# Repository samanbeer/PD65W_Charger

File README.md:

# PD65W Smart Charger 

---

## Project Overview

- **What is it?**  It is a fast 65W charger with Powerdelivery, but its SMART! It has XIAO RP2040 MCU inside and if you want to know more then read more below! 
- **What does it do?**  Belive or not its charging phone :O   Well, it is also charging modern notebooks and all other things, that have USB-C, with a maximum power of 65W which is really good. And WHILE it is charging your device, the RP2040 is with help of INA226 chip measuring input/output Voltage and Current and displaing it on 128x32 display. 
Also the chragers can be really hot while charging, but not this one. Why? Because this one has a FAN! And if the RP2040 starts to measure big temperature on thermistors then it will adjust FAN speed to cool it off.
- **Why does it exist?** Because normal charger from shops are boring, and with this charger you can see how much current and how big voltage is flowing to your phone! But also a good point why does this exist is to **reuse** old adapters from laptops or routers that have 9-24V.

---

## Why I Made This

A few months ago, I bought a small PD65W module on AliExpress to charge my phone and laptop from old 20V laptop adapter. I designed a simple 3D printed enclosure for it (which I also shared on [MakerWorld](https://makerworld.com/en/models/3175390-mini-pd-65w-trigger-charger-8-30v-case#profileId-3590634)). 

But when I connected a 65W power bank, and it was running at max power, the module and adapter was extremely hot! I also taped 10kΩ thermistor on the top of the power source on surface and I measured with multimeter temperatures over 55°C, and the internal heat was melting the PLA enclosure. And yes, I could just print it in PETG or ASA but that would not solve problem for this extreme heat.

That inspired me to build a complete, custom PCB based smart charger that fixes issues of that old setup:

1. **Cooling:** Added a 25x25x6mm 5V fan with holes for intake and exhaust
2. **2 Thermistors:** One thermistor is directly on the PD65W module, and second one is monitoring enclosure temperature
3. **OLED Display:** "0.91" OLED screen displays input voltage, input current, output voltage, output current, total wattage, temperatures, and fan speed **All in real time**.
5. **And lot more**

---

## Project Gallery

### 3D PCB Renders

### 3D Board Views

### PCB Layout & Schematic

### 3D Enclosure (Fusion 360)
*Custom 3D printable enclosure designed in Fusion 360. All CAD and 3D model files (`.f3z`, `.step`) are located in the [`CAD/`](CAD/) folder.*

---

### Schematic Blocks:

1. **AP63205 Step-Down Regulator:**
   - Steps down the 9V–24V DC input to a stable, clean **5.0V** (up to 2A) to power the XIAO RP2040, the 0.91" OLED display, and the 5V fan.
   - Uses a 4.7µH high-current power inductor (`L1`) and ceramic filter capacitors (`C2`, `C3`, `C4`).
2. **INA226:**
   - Sits on the primary input DC track through a precision 10mΩ (2512 size) shunt resistor (`R5`).
   - Communicates with the RP2040 over I2C (Address `0x40`), providing millivolt and milliamp precision for input power measurements.
3. **Output Voltage and Power calculation:**
   - A 100kΩ / 10kΩ precision resistor divider (`R6`, `R7`) scales down the 0V–20V USB-PD output rail to a safe 0V–1.82V signal for the RP2040 ADC (`A2`).
   - The firmware combines measured input power with known module conversion efficiency (~92%) and measured output voltage to calculate real time output current and power.
4. **2 Thermistors and Intelligent Fan:**
   - The cooling fan is controlled through a 2N2222 transistor (`Q1`) with a 1N4148 flyback diode (`D1`). If temperatures stay under 35°C, the fan stays completely silent (0% PWM). Between 35°C and 60°C, the fan dynamically scales speed (70–255 PWM). If temperature exceeds 60°C, the fan spins up at full 100% speed.

---

## Assembly Guide

### Required Tools & Materials
- Soldering iron 
- Some good solder wire
- Solder flux 
- Tweezers
- 3D Printer (for printing the Fusion 360 case in PETG, ABS, or PLA)
- Thermal paste or thermal conductive tape (for NTC thermistor contact)

### Assembly Steps

1. **Solder SMD ICs (U4, U5):**
   - Apply flux to the footprint pads of the **AP63205** (U4, TSOT-23-6) and **INA226** (U5, TSSOP-10).
   - Tack one corner pin, align all pins accurately under magnification, and solder the remaining pins.
2. **Solder SMD Passives & Inductor:**
   - Solder the 10mΩ 2512 shunt resistor (`R5`).
   - Solder 0805 SMD resistors (`R1–R4`, `R6–R9`) and capacitors (`C1–C6`).
   - Solder the 4.7µH power inductor (`L1`).
3. **Solder Through-Hole Components:**
   - Solder the 2N2222 transistor (`Q1`), 1N4148 diode (`D1`), and 2-pin Fan pin header (`J3`).
   - Solder the DC Barrel Jack (`J1`). There must be a good contact so put a lot of solder here.
4. **Modules:**
   - Solder the **XIAO RP2040** (`U3`) using female headers or solder direct-to-board as a SMD.
   - Solder the **PD65W Module** (`U1`) and connect the power output feedback wire (`J2`) between the module's positive output terminal and the voltage divider pad.
   - Mount the **0.91" I2C OLED Display** (`U2`) to the I2C header pins.
5. **Thermistors (TH1, TH2):**
   - Solder the thermistor.
   - Fasten `TH1` against the PD65W module power inductor/MOSFETs using thermal tape.
   - Position `TH2` near the board center to monitor ambient enclosure temperature.
6. **Final Case & Fan Assembly:**
   - Mount the 25mm 5V fan into the 3D-printed enclosure exhaust port and plug its 2-pin connector into `J3`.
   - Place the PCB and OLED into the case mounting hole and fasten with some tape.

---

## Firmware & Software Setup

### 1. Required Libraries
Install the following libraries via the Arduino IDE Library Manager:
- `INA226_WE` (by Wolfgang Ewald)
- `Adafruit GFX Library` (by Adafruit)
- `Adafruit SSD1306` (by Adafruit)
- `Wire` (Standard I2C library) - should be included

### 2. Flashing the XIAO RP2040
1. Connect the Seeed XIAO RP2040 to your computer via USB-C while holding down the **`BOOT`** button (or select the board port in Arduino IDE).
2. Select Board: **Seeed Studio XIAO RP2040** 
3. Open [`Firmware/code.ino`](Firmware/code.ino).
4. Click **Upload**.
5. Once uploaded, the OLED will start and will show all tha data.

### 3. OLED Telemetry Display Breakdown

```text
+-----------------------+
| IN :  24.00V  3.20A   |  <-- DC Barrel Jack Input
| OUT:  20.00V  2.95A   |  <-- USB-PD Output to Device
| PWR:  62.4W           |  <-- Total Active Power
| T1:42C T2:36C FAN:45% |  <-- Module Temp, Board Temp, Fan speed
+-----------------------+
```

---

## 📦 Bill of Materials (BOM)

> Sourced from [TME.eu](https://tme.eu), [AliExpress](https://aliexpress.com)

| Reference | Qty | Value / Component | Footprint / Package | Source / Link | Cost (USD) |
| :--- | :---: | :--- | :--- | :--- | :---: |
| **C1, C4, C5** | 3 | 100nF 50V MLCC | 0805 SMD | [TME Link](https://www.tme.eu/cz/details/cc0805krx7r9bb104/kondenzatory-mlcc-smd/yageo/) | $0.65 |
| **C2, C6** | 2 | 10µF 50V MLCC | 0805 SMD | [TME Link](https://www.tme.eu/cz/details/c2012x5r1v106kac/kondenzatory-mlcc-smd/tdk/c2012x5r1v106k125ac/) | $1.10 |
| **C3** | 1 | 22µF 16V MLCC | 0805 SMD | [TME Link](https://www.tme.eu/cz/details/cl21a226kpclrnc/kondenzatory-mlcc-smd/samsung/) | $0.39 |
| **D1** | 1 | 1N4148 Fast Switching Diode | DO-35 / DO-41 THT | [TME Link](https://www.tme.eu/cz/details/1n4148-cdi/univerzalni-diody-tht/cdil/1n4148/) | $0.1 |
| **J1** | 1 | DC Barrel Jack | Horizontal THT Barrel Jack | [TME Link](https://www.tme.eu/cz/details/fcr681465p/konektory-dc/cliff/fc681465p-dc-10lp/) | $2.42 |
| **J3** | 1 | 2-Pin Fan Header (2.54mm) + Sunon 5V Fan | PinHeader 1x02 + 25x25x6mm Fan | [TME Link](https://www.tme.eu/cz/details/mf25060v1-a99-a/ventilatory-dc-5v/sunon/mf25060v1-1000u-a99/) | $7.90 |
| **L1** | 1 | 4.7µH Power Inductor | SMD 6.3x6.3mm (LSXND6060) | [TME Link](https://www.tme.eu/cz/details/lsxnd6060yel4r7nmg/tlumivky/taiyo-yuden/) | $0.50 |
| **Q1** | 1 | 2N2222 NPN Transistor | TO-92 THT | [TME LInk](https://www.tme.eu/cz/details/2n2222a-dio/tranzistory-npn-tht/diotec-semiconductor/2n2222a/) | $0.90 |
| **R1, R2, R3, R4, R7, R9** | 6 | 10kΩ | 0805 SMD | [TME Link](https://www.tme.eu/cz/details/crcw080510k0fkea/rezistory-smd/vishay/) | $0.084 |
| **R5** | 1 | 10mΩ (0.010Ω) 1% Current Shunt | 2512 High-Power SMD | [TME Link](https://www.tme.eu/cz/details/mar251202fr010s/rezistory-smd/wayon/) | $1.98 |
| **R6** | 1 | 100kΩ 1% Resistor | 0805 SMD | [TME Link](https://www.tme.eu/cz/details/rc0805fr-07100k/rezistory-smd/yageo/rc0805fr-07100kl/) | $0.070 |
| **R8** | 1 | 1kΩ 1% Resistor | 0805 SMD | [TME Link](https://www.tme.eu/cz/details/rc0805fr-071k/rezistory-smd/yageo/rc0805fr-071kl/)  | $0.042 |
| **TH1, TH2** | 2 | 10kΩ NTC Thermistors (B=3950) | Radial / Axial THT | [TME Link](https://www.tme.eu/cz/details/b57891m0103j000/merici-termistory-ntc-tht/tdk/) | $1.45 |
| **U1** | 1 | PD65W USB-C PD Step-Down Module | Custom Module Footprint | [AliExpress Link](https://www.aliexpress.com/item/1005012593373561.html) | $6.00 |
| **U2** | 1 | 0.91" I2C Monochrome OLED Display | 4-Pin I2C Module Header | [AliExpress Link](https://www.aliexpress.com/item/1005008918700196.html) | $5.50 |
| **U3** | 1 | Seeed Studio XIAO RP2040 MCU | XIAO DIP-14 Module | [TME Link](https://www.tme.eu/cz/details/seeed-102010428/vyvojove-kity-ostatni/seeed-studio/xiao-rp2040/) | $7.00 |
| **U4** | 1 | AP63205WU 5V 2A Buck Regulator | TSOT-23-6 SMD | [AliExpress Link](https://www.aliexpress.com/item/1005006407229203.html) | $4.00 |
| **U5** | 1 | INA226AIDGSR Power Monitor IC | TSSOP-10 SMD | [TME Link](https://www.tme.eu/cz/details/ina226aidgsr/operacni-zesilovace-smd/texas-instruments/) | $6.00 |
| **PCB** | 1 | 2-Layer Custom FR-4 PCB (1.6mm) | Custom KiCad Design | [JLCPCB](https://jlcpcb.com) | $9.53 |
| **Shipping** | - | Combined Estimated Shipping | - | AliExpress & TME.eu | ~$10.00 |
| **Total** | | | | | **~$65.62** |

>btw you can import every components that is from TME directly to TME cart with this file: [quick_order_TME.csv](PCB/quick_order_TME.csv) 

---

## 🚀 How to Use

1. **Connect DC Power:** Plug any 9V to 24V DC power source (almost every old laptop charger) into the rear barrel jack `J1`.
2. **System Initialization:** The OLED display will lights up, showing the measured input voltages and temperatures.
3. **Charge your Device!:** Just connect anything you have with USB-C! (even laptops)
4. **Automatic Cooling:** Under heavy sustained loads (e.g., 45W–65W), the internal fan will automatically spin up smoothly based on thermistor readings, keeping components well within safe operating temperatures.

---

- Designed by **Šámot** in [Hack Club Forge](https://forge.hackclub.com/projects/1660) project.

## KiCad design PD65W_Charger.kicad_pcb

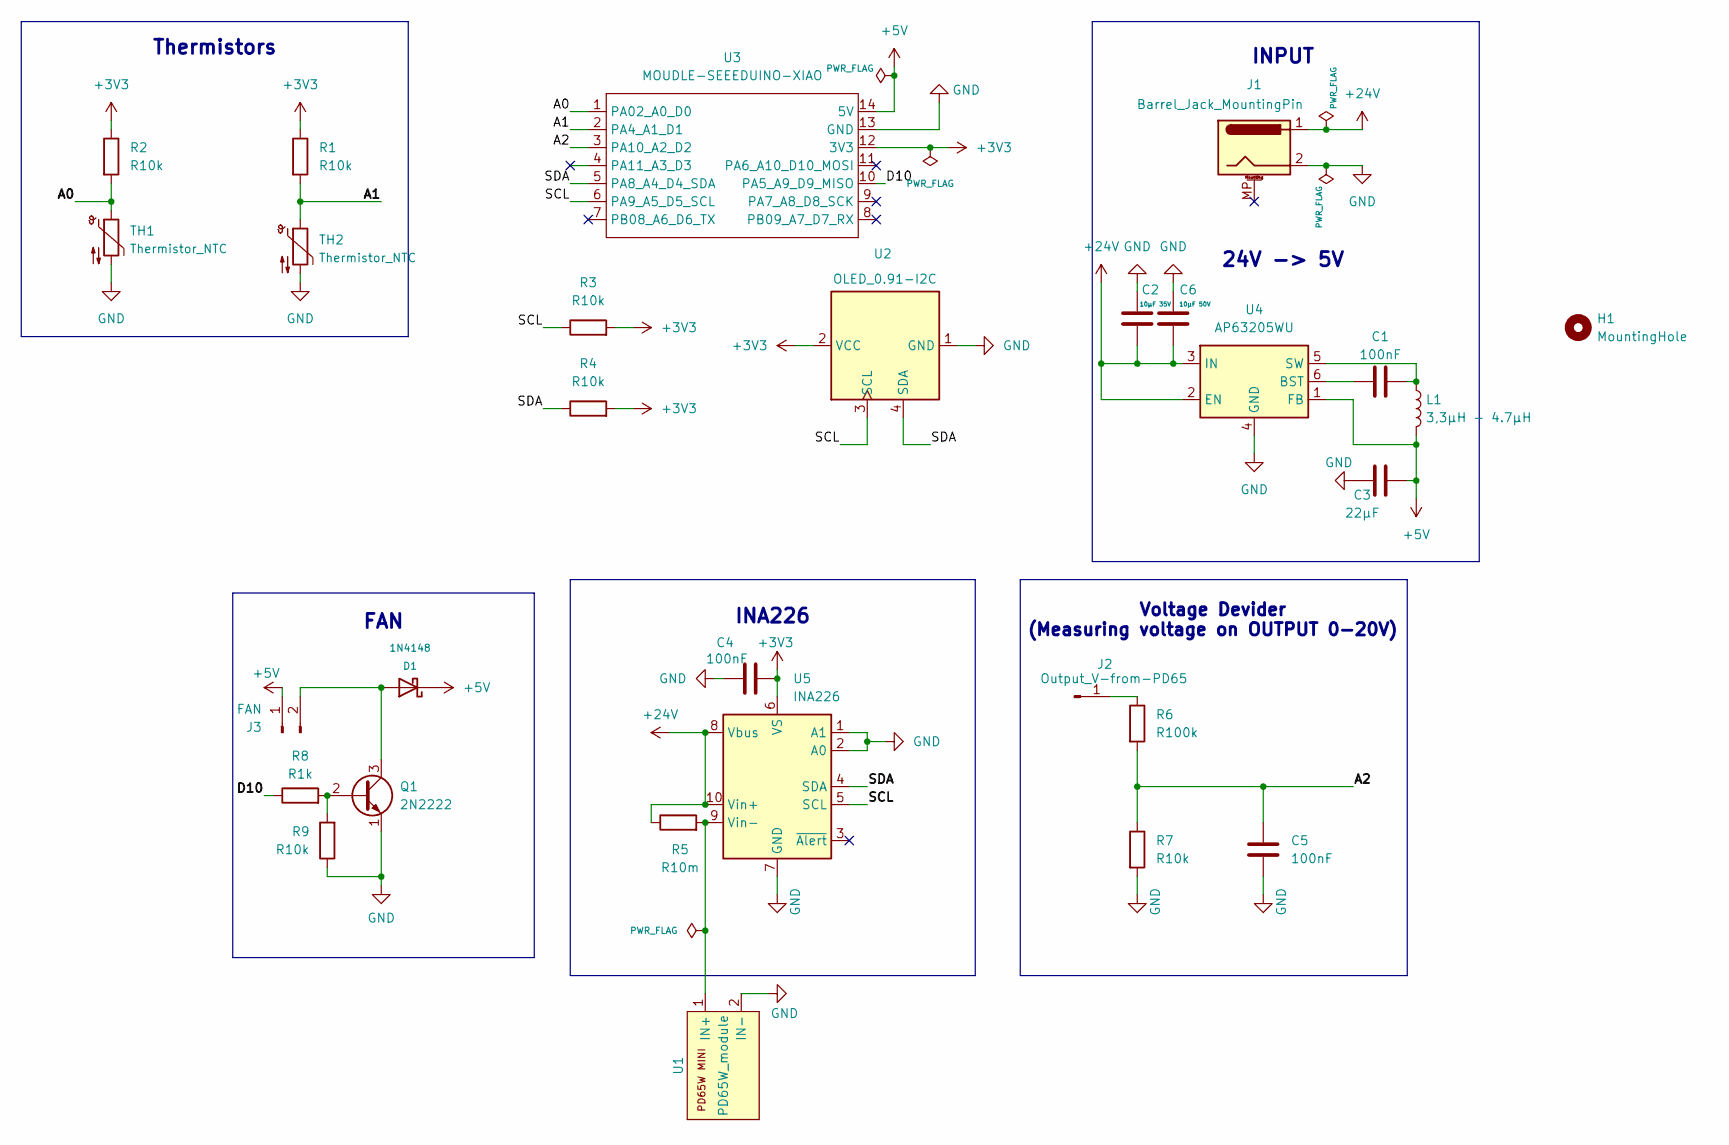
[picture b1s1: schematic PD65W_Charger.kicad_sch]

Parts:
C1, C4, C5: 100nF; C_0805_2012Metric_Pad1.18x1.45mm_HandSolder
C2: 10µF 35V; C_0805_2012Metric_Pad1.18x1.45mm_HandSolder
C3: 22µF; C_0805_2012Metric_Pad1.18x1.45mm_HandSolder
C6: 10µF 50V; C_0805_2012Metric_Pad1.18x1.45mm_HandSolder
D1: 1N4148; D_DO-41_SOD81_P7.62mm_Horizontal
H1: MountingHole; MountingHole_3.2mm_M3_DIN965
J1: Barrel_Jack_MountingPin; BarrelJack_Horizontal
J2: Output_V-from-PD65; SolderWire-1sqmm_1x01_D1.4mm_OD2.7mm
J3: FAN; PinHeader_1x02_P2.54mm_Vertical
L1: 3,3µH - 4.7µH; L_6.3x6.3_H3
Q1: 2N2222; TO-92
R1, R2, R3, R4, R7, R9: R10k; R_0805_2012Metric_Pad1.20x1.40mm_HandSolder
R5: R10m; R_2512_6332Metric_Pad1.40x3.35mm_HandSolder
R6: R100k; R_0805_2012Metric_Pad1.20x1.40mm_HandSolder
R8: R1k; R_0805_2012Metric_Pad1.20x1.40mm_HandSolder
TH1, TH2: Thermistor_NTC; R_Axial_DIN0309_L9.0mm_D3.2mm_P2.54mm_Vertical
U1: PD65W_module
U2: OLED_0.91-I2C; ER_OLEDM0.91_1x-I2C
U3: MOUDLE-SEEEDUINO-XIAO; XIAO-RP2040-DIP
U4: AP63205WU; TSOT-23-6_HandSoldering
U5: INA226; TSSOP-10_3x3mm_P0.5mm

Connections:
+3V3: C4.2, R1.1, R2.1, R3.2, R4.2, U2.2 (VCC), U3.12 (3V3), U5.6 (VS)
+5V: C3.2, D1.1 (K), J3.1, L1.2, U3.14 (5V), U4.1 (FB)
+24V: C2.2, C6.2, J1.1, R5.1, U4.2 (EN), U4.3 (IN), U5.8 (Vbus), U5.10 (Vin+)
/A0: R2.2, TH1.1, U3.1 (PA02_A0_D0)
/A1: R1.2, TH2.1, U3.2 (PA4_A1_D1)
/A2: C5.1, R6.2, R7.1, U3.3 (PA10_A2_D2)
/D10: R8.1, U3.10 (PA5_A9_D9_MISO)
/SCL: R3.1, U2.3 (SCL), U3.6 (PA9_A5_D5_SCL), U5.5 (SCL)
/SDA: R4.1, U2.4 (SDA), U3.5 (PA8_A4_D4_SDA), U5.4 (SDA)
GND: C2.1, C3.1, C4.1, C5.2, C6.1, J1.2, Q1.1 (E), R7.2, R9.1, TH1.2, TH2.2, U1.2 (IN-), U2.1 (GND), U3.13 (GND), U4.4 (GND), U5.1 (A1), U5.2 (A0), U5.7 (GND)
unnamed: D1.2 (A), J3.2, Q1.3 (C)
unnamed: J2.1 (Pin_1_1), R6.1
unnamed: Q1.2 (B), R8.2, R9.2
unnamed: R5.2, U1.1 (IN+), U5.9 (Vin-)
unnamed: C1.1, U4.6 (BST)
unnamed: C1.2, L1.1, U4.5 (SW)

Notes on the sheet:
INPUT
Voltage Devider (Measuring voltage on OUTPUT 0-20V)
Thermistors
FAN
24V -> 5V
INA226

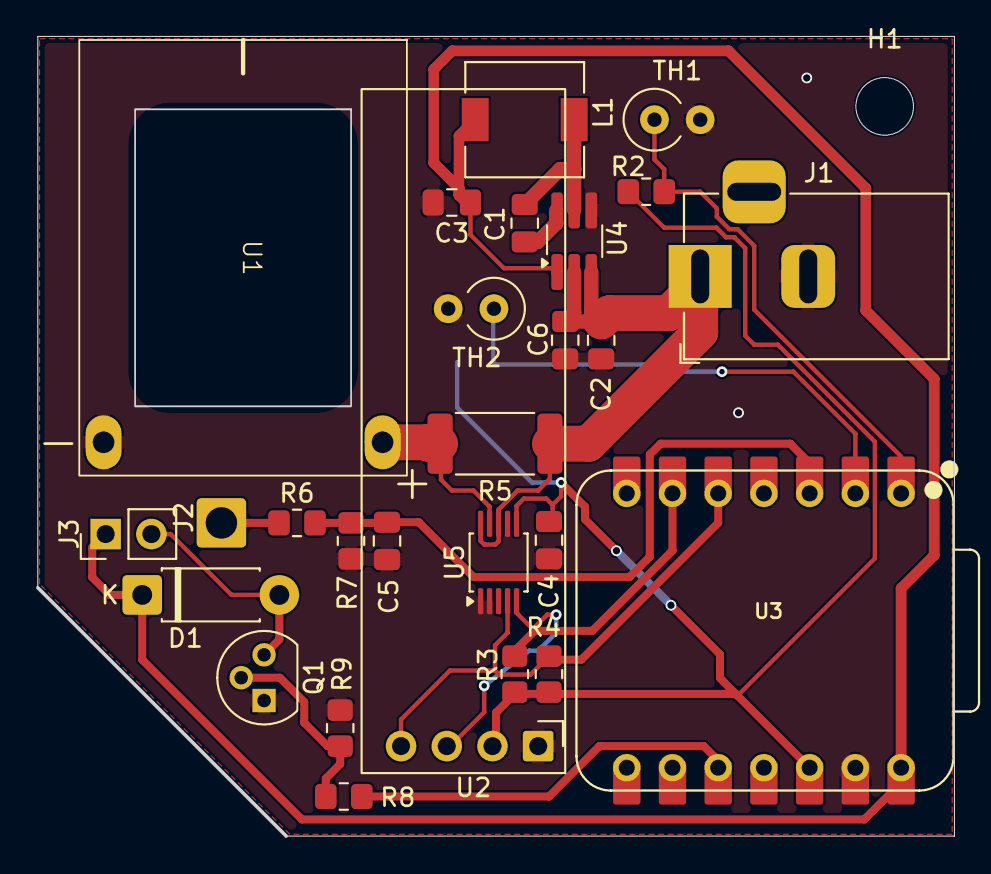
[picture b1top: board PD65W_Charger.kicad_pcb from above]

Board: 2 copper layers, 50.9 x 44.4 mm, 29 parts (1 on the bottom side), 16 nets.

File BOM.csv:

"Reference","Qty","Value","DNP","Exclude from BOM","Exclude from Board","Footprint"
"C1,C5","2","100nF","","","","Capacitor_SMD:C_0805_2012Metric_Pad1.18x1.45mm_HandSolder"
"C2","1","10µF 50V","","","","Capacitor_SMD:C_0805_2012Metric_Pad1.18x1.45mm_HandSolder"
"C3","1","22µF","","","","Capacitor_SMD:C_0805_2012Metric_Pad1.18x1.45mm_HandSolder"
"C4","1","100nF","","","","Capacitor_SMD:C_0805_2012Metric"
"D1","1","1N4148","","","","Diode_THT:D_DO-41_SOD81_P7.62mm_Horizontal"
"J1","1","Barrel_Jack_MountingPin","","","","Connector_BarrelJack:BarrelJack_GCT_DCJ200-10-A_Horizontal"
"J2","1","Output_V-from-PD65","","","","Connector_Wire:SolderWire-1sqmm_1x01_D1.4mm_OD2.7mm"
"J3","1","FAN","","","","Connector_PinHeader_2.54mm:PinHeader_1x02_P2.54mm_Vertical"
"L1","1","3,3µH - 4.7µH","","","","Inductor_SMD:L_Bourns-SRN4018"
"Q1","1","2N2222","","","","Package_TO_SOT_THT:TO-92"
"R1,R2,R3,R4,R7,R9","6","R10k","","","","Resistor_SMD:R_0805_2012Metric_Pad1.20x1.40mm_HandSolder"
"R5","1","R10m","","","","Resistor_SMD:R_2512_6332Metric_Pad1.40x3.35mm_HandSolder"
"R6","1","R100k","","","","Resistor_SMD:R_0805_2012Metric_Pad1.20x1.40mm_HandSolder"
"R8","1","R1k","","","","Resistor_SMD:R_0805_2012Metric_Pad1.20x1.40mm_HandSolder"
"TH1,TH2","2","Thermistor_NTC","","","","Resistor_THT:R_Axial_DIN0309_L9.0mm_D3.2mm_P2.54mm_Vertical"
"U1","1","PD65W_module","","","","Library_footprint:PD65W_module"
"U2","1","OLED_0.91-I2C","","","","Display:ER_OLEDM0.91_1x-I2C"
"U3","1","MOUDLE-SEEEDUINO-XIAO","","","","Seeed Studio XIAO Series Library:XIAO-RP2040-DIP"
"U4","1","AP63205WU","","","","Package_TO_SOT_SMD:TSOT-23-6_HandSoldering"
"U5","1","INA226","","","","Package_SO:TSSOP-10_3x3mm_P0.5mm"

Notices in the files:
README.md:
License: MIT
